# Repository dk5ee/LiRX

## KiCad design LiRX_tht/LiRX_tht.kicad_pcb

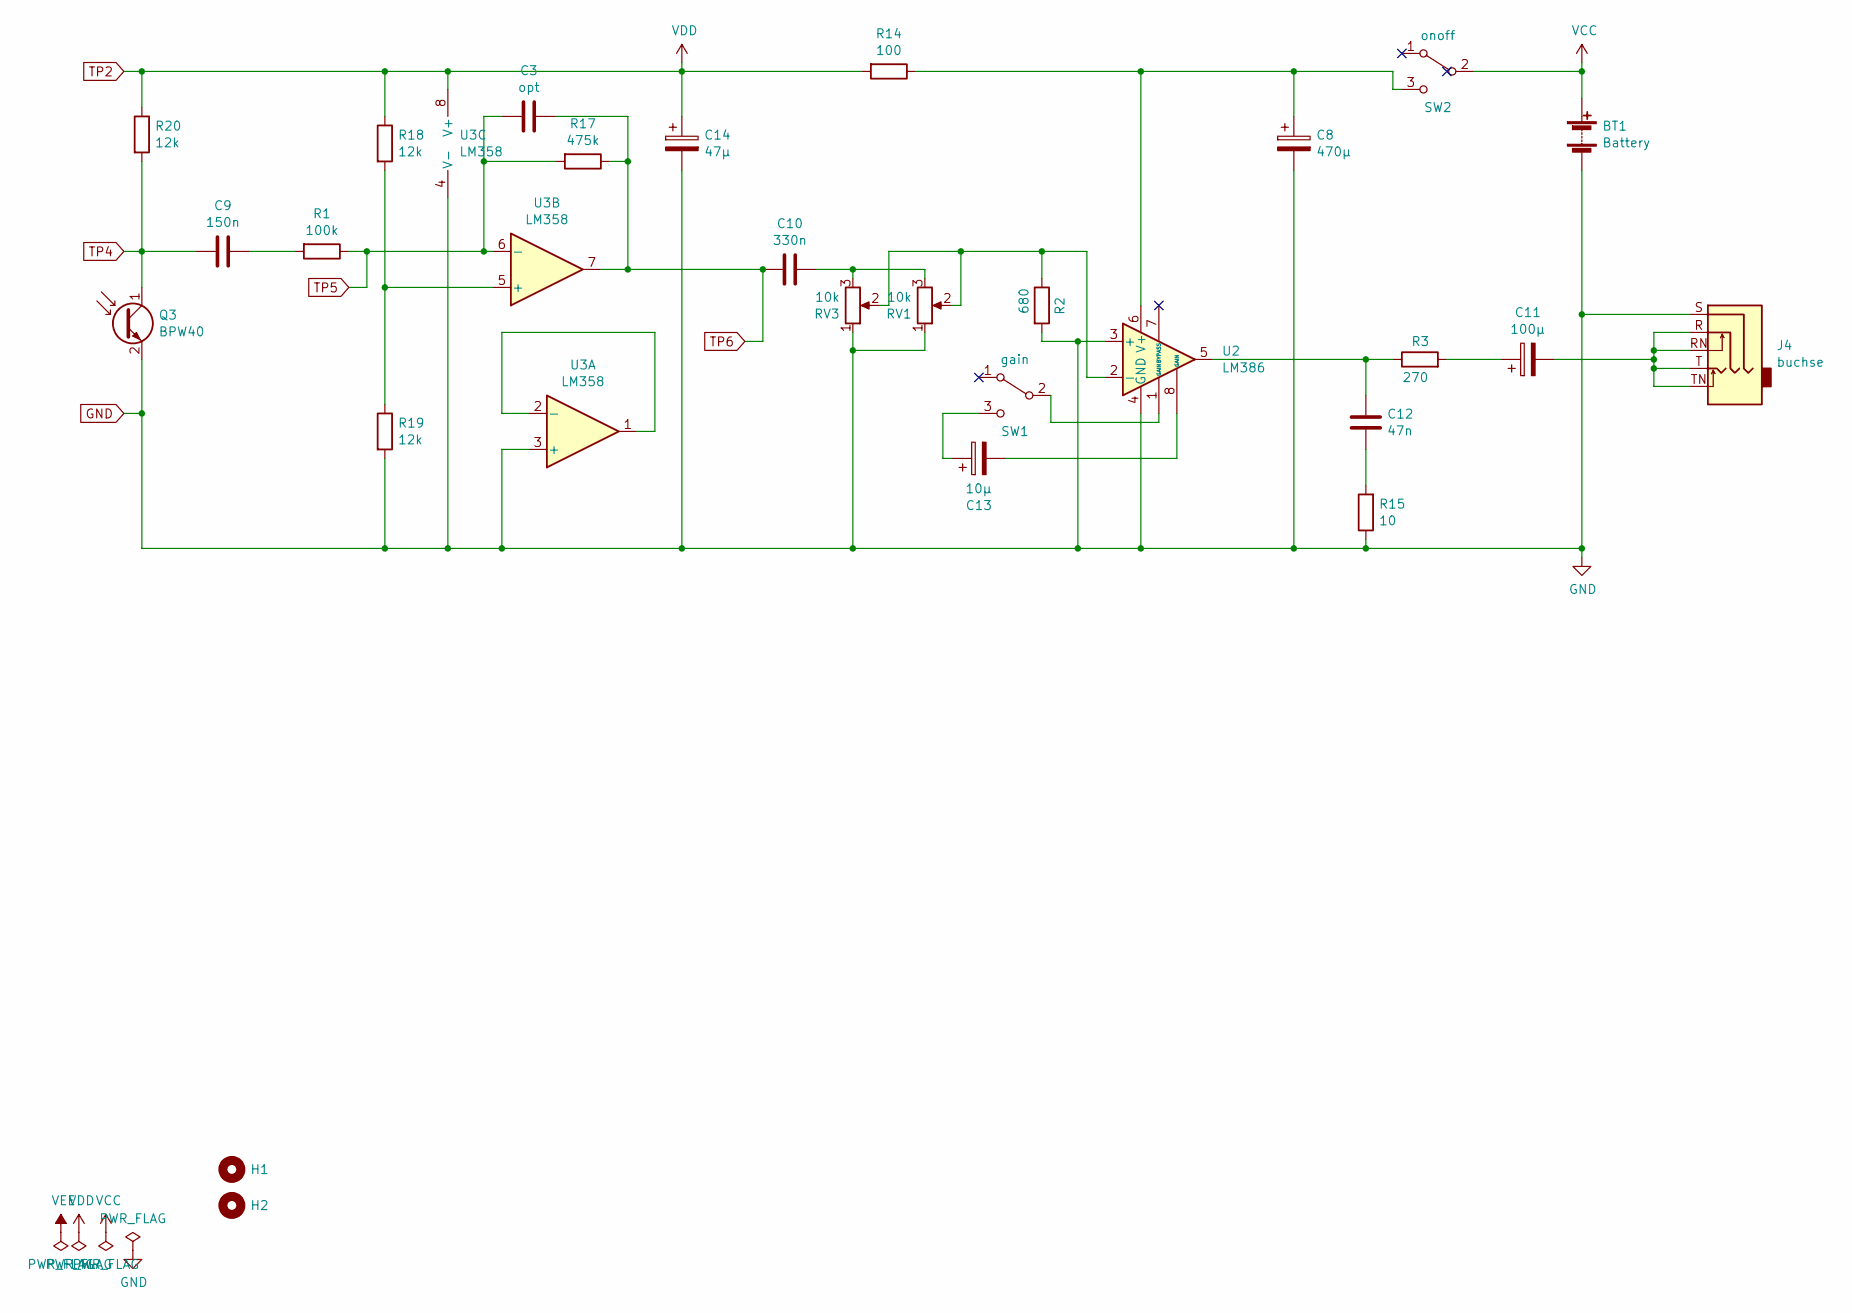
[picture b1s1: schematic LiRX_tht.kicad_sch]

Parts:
BT1: Battery; PinHeader_1x02_P2.54mm_Vertical
C3: opt; C_Disc_D3.0mm_W1.6mm_P2.50mm
C8: 470µ; CP_Radial_D10.0mm_P2.50mm_P5.00mm
C9: 150n; C_Rect_L7.0mm_W3.5mm_P2.50mm_P5.00mm
C10: 330n; C_Rect_L7.0mm_W3.5mm_P2.50mm_P5.00mm
C11: 100µ; CP_Radial_D5.0mm_P2.00mm
C12: 47n; C_Disc_D3.0mm_W1.6mm_P2.50mm
C13: 10µ; CP_Radial_D5.0mm_P2.00mm
C14: 47µ; CP_Radial_D5.0mm_P2.00mm
H1, H2: MountingHole; MountingHole_3.2mm_M3
J4: buchse; Jack_3.5mm_Ledino_KB3SPRS_Horizontal
Q3: BPW40; LED_D5.0mm_Horizontal_O1.27mm_Z3.0mm_Clear
R1: 100k; R_Axial_DIN0204_L3.6mm_D1.6mm_P7.62mm_Horizontal
R2: 680; R_Axial_DIN0204_L3.6mm_D1.6mm_P7.62mm_Horizontal
R3: 270; R_Axial_DIN0204_L3.6mm_D1.6mm_P7.62mm_Horizontal
R14: 100; R_Axial_DIN0204_L3.6mm_D1.6mm_P7.62mm_Horizontal
R15: 10; R_Axial_DIN0204_L3.6mm_D1.6mm_P7.62mm_Horizontal
R17: 475k; R_Axial_DIN0204_L3.6mm_D1.6mm_P7.62mm_Horizontal
R18, R19, R20: 12k; R_Axial_DIN0204_L3.6mm_D1.6mm_P7.62mm_Horizontal
RV1: 10k; Potentiometer_Piher_T-16H_Single_Horizontal
RV3: 10k; Potentiometer_Piher_PC-16_Single_Horizontal
SW1: gain; SW_CuK_OS102011MA1QN1_SPDT_Angled
SW2: onoff; SW_CuK_OS102011MA1QN1_SPDT_Angled
U2: LM386; DIP-8_W7.62mm_LongPads
U3: LM358; DIP-8_W7.62mm_LongPads

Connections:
GND: BT1.2 (-), C8.2, C14.2, J4.S, Q3.2 (E), R2.2, R15.1, R19.2, RV1.1, RV3.1, U2.3 (+), U2.4 (GND), U3.3 (+), U3.4 (V-)
unnamed: C8.1, R14.1, SW2.3 (C), U2.6 (V+)
unnamed: C9.1, R1.2
unnamed: C10.1, RV1.3, RV3.3
unnamed: C11.1, R3.2
unnamed: C11.2, J4.R, J4.RN, J4.T, J4.TN
unnamed: C12.1, R3.1, U2.5
unnamed: C12.2, R15.2
unnamed: C13.1, SW1.3 (C)
unnamed: C13.2, U2.8 (GAIN)
unnamed: R2.1, RV1.2, RV3.2, U2.2 (-)
unnamed: R18.2, R19.1, U3.5 (+)
unnamed: SW1.2 (B), U2.1 (GAIN)
unnamed: U3.1, U3.2 (-)
TP2: C14.1, R14.2, R18.1, R20.1, U3.8 (V+)
TP4: C9.2, Q3.1 (C), R20.2
TP5: C3.2, R1.1, R17.2, U3.6 (-)
TP6: C3.1, C10.2, R17.1, U3.7
VCC: BT1.1 (+), SW2.2 (B)

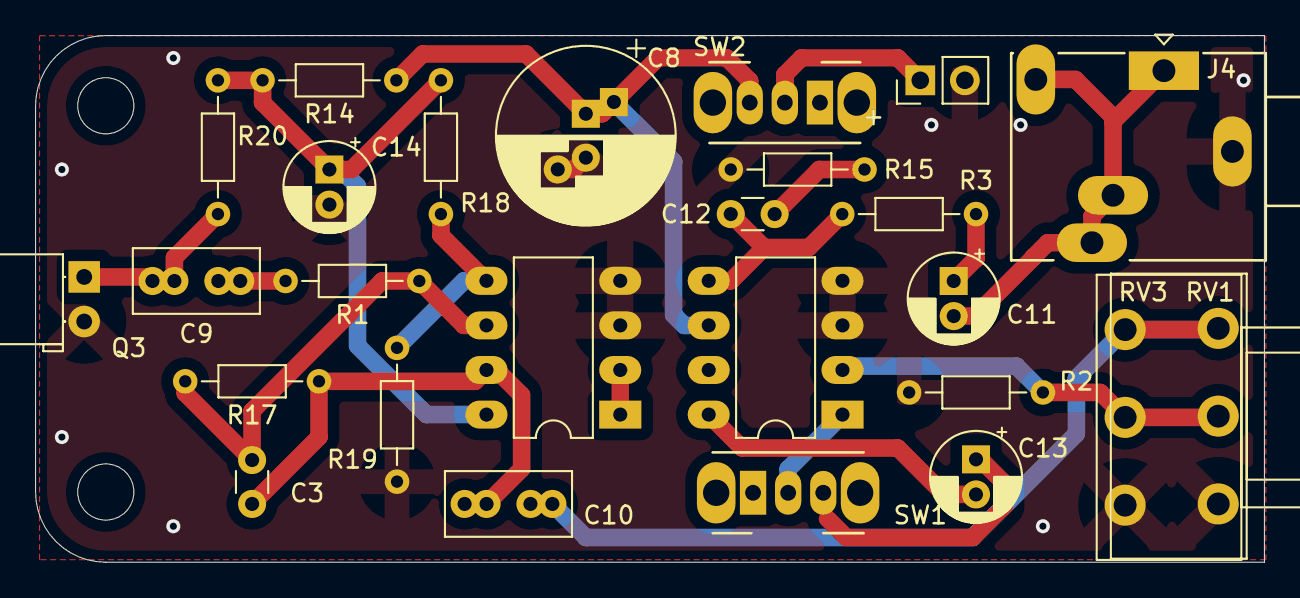
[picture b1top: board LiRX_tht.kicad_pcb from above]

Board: 2 copper layers, 70.0 x 30.0 mm, 28 parts (0 on the bottom side), 19 nets.

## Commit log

2021-10-11 add logbook
2021-10-11 import Kicad schematics and PCB
2021-10-11 cleanup and plot
2021-10-11 logentry
2021-10-11 Versandkosten
2021-10-14 Bauteilhinweis
2021-10-14 correct gitignore to include BOM
2021-10-14 Added DXF files
2021-10-23 picture of prototype
2021-10-26 Schematic PDF
2021-10-26 testpoints
2021-10-28 gitignore tex
2021-10-28 Anleitung
2022-01-05 Added Suggestions; 1cm longer; kicad 6.0
2022-01-14 nutzen
2022-01-14 Anleitung verbessert
2022-03-31 Add files via upload
    Lightburn Projekt für Gehäuse. Fehlt noch Loch für Klammer und Schalter soll versetzt werden.
2022-04-21 Add files via upload
    kleinere Anpassungen. Schalter jetzt hinten
2022-10-06 neues Gehaeuse auf 3mm
2022-10-06 Lirex neues Gehaeuse 3m Lightburn Project
